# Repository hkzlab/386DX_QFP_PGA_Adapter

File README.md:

# 386DX QFP -> PGA Adapter

## Introduction

386DX CPUs in ceramic PGA packages are getting rarer and more expensive by the day, while QFP variants can still be found relatively easily. But some motherboards don't have a space for a QFP CPU, and they're an hassle to swap anyway.

This project provides a way to adapt the QFP variants of the 386DX cpus to a PGA format, by using commonly available hardware parts.
I tested the procedure on an AM386DX @ 40Mhz, and the machine happily ran memory tests and benchmarks for hours.

### Disclaimer

I take NO responsibility for what happens if you decide to build and use this adapter. But You're encourauged to take what you deem fit from this, and use it in your projects!

## Required components

* The PCB adapter itself, 1.6mm thickness is fine
* The pin holder, 1.6mm thickness
* Stencil for the bottom (PGA) side of the adapter
* Solder paste for SMD work
* Pin sockets, lots of (>132, as some will be bent, out of spec, etc.). 7.54mm for height is a good measure. You can find them on Aliexpress, e.g. [here](https://www.aliexpress.com/item/1005003484780787.html).

### How to build

1. Place the pin holder somewhere raised that leaves you access to the pin holes. I use a "helping hand" soldering tool that pinches the holder at the corners and leaves free the top and bottom of it.
2. Install all the pins from the top. They don't have to snap. It is sufficient that they slide into every hole and stay flush on top. Make sure the height is the same for every pin.
3. Put the QFP-PGA adapter PCB on a flat surface, PGA side (the one with all the "squares") on top.
4. Using the stencil, apply the solder paste evenly on every square where the pins are going to go
5. Carefully lift the adapter PCB, flip it, and put the PGA side on top of the holder with pins (the one currently mounted on the helping hand), making sure that the edges of both PCBs are aligned. You'll get a sandwich of the adapter and holder with the "heads" of the pin in between.
6. Release the holder from the helping hand and flip both the holder and the adapter PCB together, and place them on a flat, heat resistant surface (I use vetronite), with pins pointing towards the ceiling.
7. Turn on your hot air soldering station, and slowly begin soldering all the pins, first heating everything then working on all the sides of the adapter, trying to blow directly on the pins.
8. Pins will start to move slightly, as the flux evaporates. Keep circling around. When they stop moving, they'll have sucked up most of the solder.
9. Wait for everything to cool down, then carefully remove the holder.
10. Inspect with a good light and magnifying glass for shorts between pins. Usually the pins will suck up the excess solder, and you'll probably find no shorts at all. Cut the shorts you find, being careful not to damage the adapter. Also, check that every pin is attached correctly.
11. If you see that some pin has not attached correctly, or is a bit raised than the rest, apply flux, holder, and re-heat.
12. Install the bypass caps if you want them.
13. Reinstall the holder for structural stability. It doesn't have to snap in. It'll hold on pretty well anyway.
14. You can now solder the processor on the completed adapter. Use a soldering iron for this.

Here are some pics at various points of the procedure. Some images refer to a V53 adapter, but the procedure is identical to the one for this CPU.

## Notes

The last tested revision of the board is Rev.1, changes to Rev.3 are minimal and mostly aesthetic, but be warned.

I tested this adapter with an AM386DX @ 40Mhz.

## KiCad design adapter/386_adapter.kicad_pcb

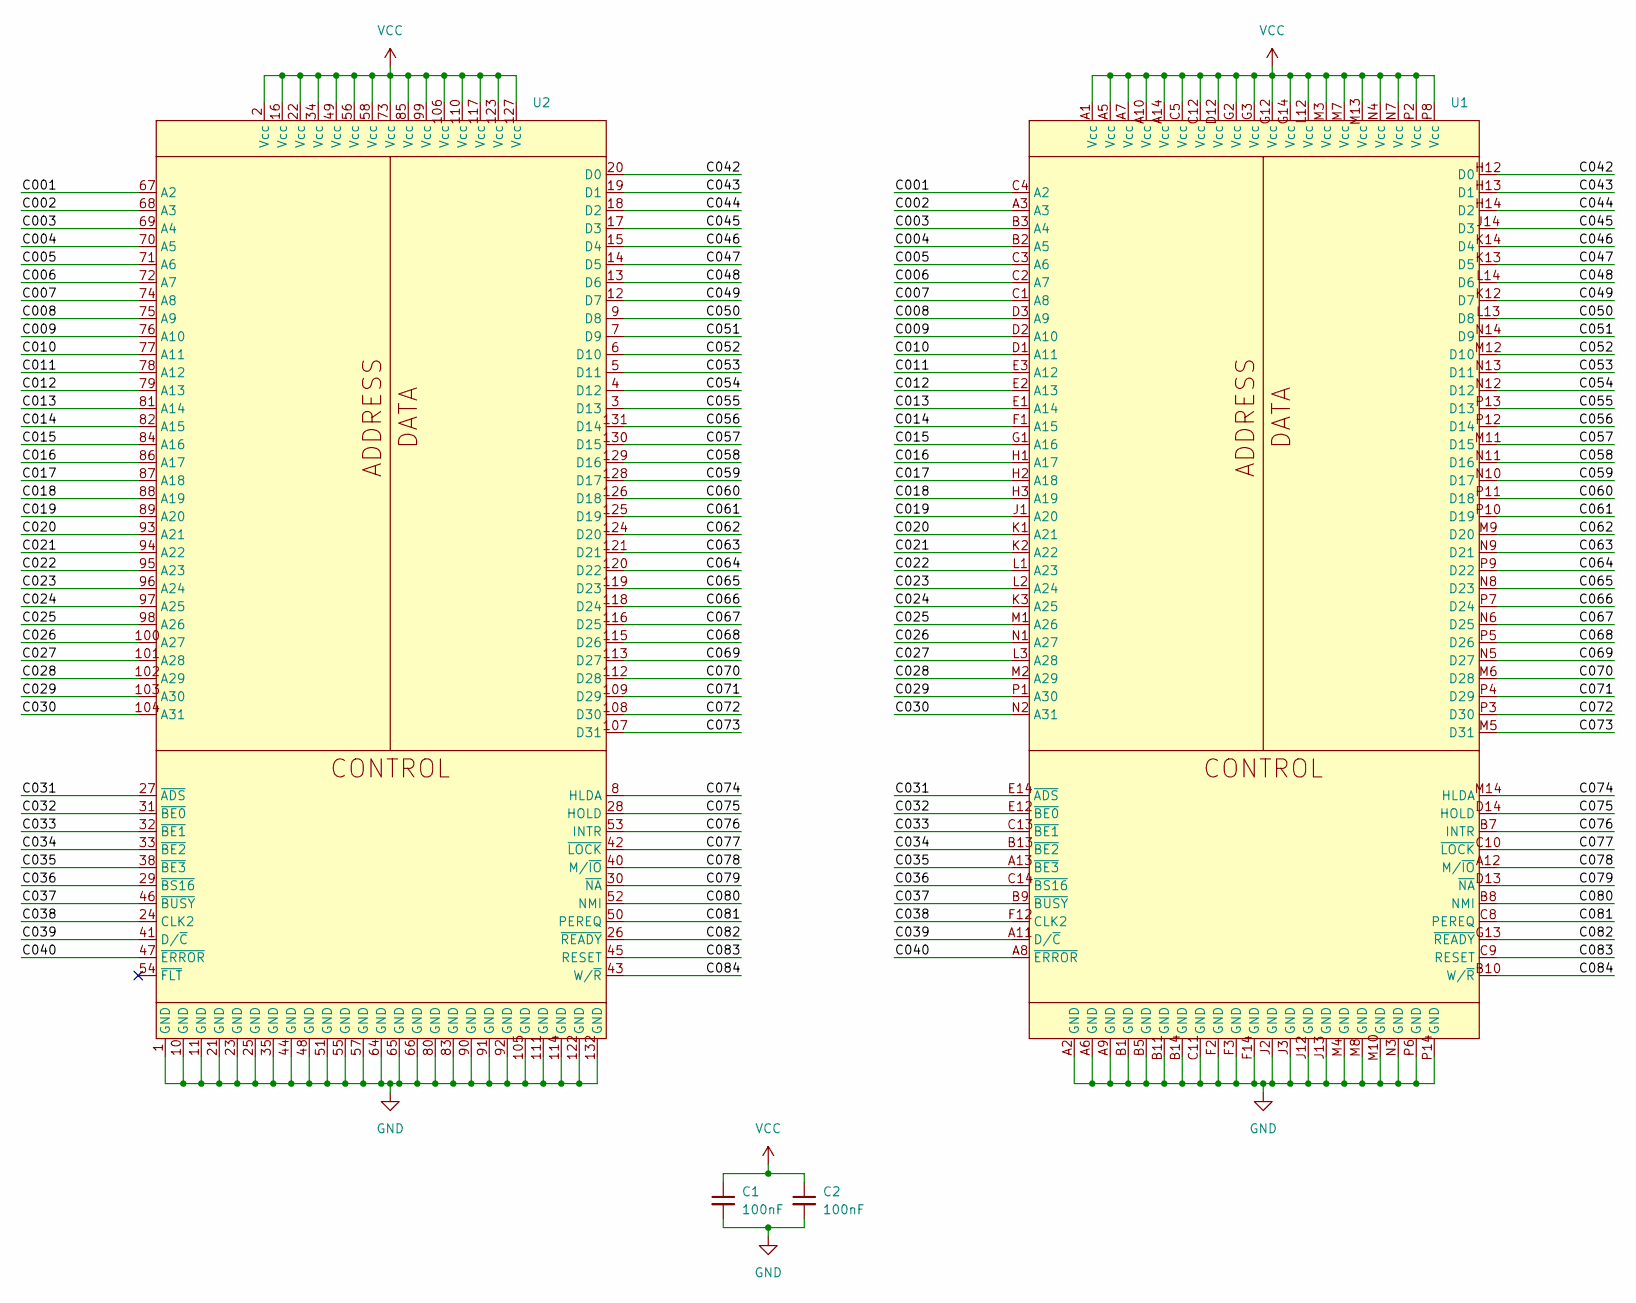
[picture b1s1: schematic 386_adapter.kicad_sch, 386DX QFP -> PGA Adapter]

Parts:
C1, C2: 100nF; C_1206_3216Metric_Pad1.33x1.80mm_HandSolder
U1: PGA-132_SMD
U2: PQFP-132_24x24mm_P0.635mm_i386

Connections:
/C001: U1.C4 (A2), U2.67 (A2)
/C002: U1.A3, U2.68 (A3)
/C003: U1.B3 (A4), U2.69 (A4)
/C004: U1.B2 (A5), U2.70 (A5)
/C005: U1.C3 (A6), U2.71 (A6)
/C006: U1.C2 (A7), U2.72 (A7)
/C007: U1.C1 (A8), U2.74 (A8)
/C008: U1.D3 (A9), U2.75 (A9)
/C009: U1.D2 (A10), U2.76 (A10)
/C010: U1.D1 (A11), U2.77 (A11)
/C011: U1.E3 (A12), U2.78 (A12)
/C012: U1.E2 (A13), U2.79 (A13)
/C013: U1.E1 (A14), U2.81 (A14)
/C014: U1.F1 (A15), U2.82 (A15)
/C015: U1.G1 (A16), U2.84 (A16)
/C016: U1.H1 (A17), U2.86 (A17)
/C017: U1.H2 (A18), U2.87 (A18)
/C018: U1.H3 (A19), U2.88 (A19)
/C019: U1.J1 (A20), U2.89 (A20)
/C020: U1.K1 (A21), U2.93 (A21)
/C021: U1.K2 (A22), U2.94 (A22)
/C022: U1.L1 (A23), U2.95 (A23)
/C023: U1.L2 (A24), U2.96 (A24)
/C024: U1.K3 (A25), U2.97 (A25)
/C025: U1.M1 (A26), U2.98 (A26)
/C026: U1.N1 (A27), U2.100 (A27)
/C027: U1.L3 (A28), U2.101 (A28)
/C028: U1.M2 (A29), U2.102 (A29)
/C029: U1.P1 (A30), U2.103 (A30)
/C030: U1.N2 (A31), U2.104 (A31)
/C031: U1.E14 (~ADS), U2.27 (~ADS)
/C032: U1.E12 (~BE0), U2.31 (~BE0)
/C033: U1.C13 (~BE1), U2.32 (~BE1)
/C034: U1.B13 (~BE2), U2.33 (~BE2)
/C035: U1.A13 (~BE3), U2.38 (~BE3)
/C036: U1.C14 (~BS16), U2.29 (~BS16)
/C037: U1.B9 (~BUSY), U2.46 (~BUSY)
/C038: U1.F12 (CLK2), U2.24 (CLK2)
/C039: U1.A11 (D/~C), U2.41 (D/~C)
/C040: U1.A8 (~ERROR), U2.47 (~ERROR)
/C042: U1.H12 (D0), U2.20 (D0)
/C043: U1.H13 (D1), U2.19 (D1)
/C044: U1.H14 (D2), U2.18 (D2)
/C045: U1.J14 (D3), U2.17 (D3)
/C046: U1.K14 (D4), U2.15 (D4)
/C047: U1.K13 (D5), U2.14 (D5)
/C048: U1.L14 (D6), U2.13 (D6)
/C049: U1.K12 (D7), U2.12 (D7)
/C050: U1.L13 (D8), U2.9 (D8)
/C051: U1.N14 (D9), U2.7 (D9)
/C052: U1.M12 (D10), U2.6 (D10)
/C053: U1.N13 (D11), U2.5 (D11)
/C054: U1.N12 (D12), U2.4 (D12)
/C055: U1.P13 (D13), U2.3 (D13)
/C056: U1.P12 (D14), U2.131 (D14)
/C057: U1.M11 (D15), U2.130 (D15)
/C058: U1.N11 (D16), U2.129 (D16)
/C059: U1.N10 (D17), U2.128 (D17)
/C060: U1.P11 (D18), U2.126 (D18)
/C061: U1.P10 (D19), U2.125 (D19)
/C062: U1.M9 (D20), U2.124 (D20)
/C063: U1.N9 (D21), U2.121 (D21)
/C064: U1.P9 (D22), U2.120 (D22)
/C065: U1.N8 (D23), U2.119 (D23)
/C066: U1.P7 (D24), U2.118 (D24)
/C067: U1.N6 (D25), U2.116 (D25)
/C068: U1.P5 (D26), U2.115 (D26)
/C069: U1.N5 (D27), U2.113 (D27)
/C070: U1.M6 (D28), U2.112 (D28)
/C071: U1.P4 (D29), U2.109 (D29)
/C072: U1.P3 (D30), U2.108 (D30)
/C073: U1.M5 (D31), U2.107 (D31)
/C074: U1.M14 (HLDA), U2.8 (HLDA)
/C075: U1.D14 (HOLD), U2.28 (HOLD)
/C076: U1.B7 (INTR), U2.53 (INTR)
/C077: U1.C10 (~LOCK), U2.42 (~LOCK)
/C078: U1.A12 (M/~IO), U2.40 (M/~IO)
/C079: U1.D13 (~NA), U2.30 (~NA)
/C080: U1.B8 (NMI), U2.52 (NMI)
/C081: U1.C8 (PEREQ), U2.50 (PEREQ)
/C082: U1.G13 (~READY), U2.26 (~READY)
/C083: U1.C9 (RESET), U2.45 (RESET)
/C084: U1.B10 (W/~R), U2.43 (W/~R)
GND: C1.2, C2.2, U1.A2 (GND), U1.A6 (GND), U1.A9 (GND), U1.B1 (GND), U1.B5 (GND), U1.B11 (GND), U1.B14 (GND), U1.C11 (GND), U1.F2 (GND), U1.F3 (GND), U1.F14 (GND), U1.J2 (GND), U1.J3 (GND), U1.J12 (GND), U1.J13 (GND), U1.M4 (GND), U1.M8 (GND), U1.M10 (GND), U1.N3 (GND), U1.P6 (GND), U1.P14 (GND), U2.1 (GND), U2.10 (GND), U2.11 (GND), U2.21 (GND), U2.23 (GND), U2.25 (GND), U2.35 (GND), U2.44 (GND), U2.48 (GND), U2.51 (GND), U2.55 (GND), U2.57 (GND), U2.64 (GND), U2.65 (GND), U2.66 (GND), U2.80 (GND), U2.83 (GND), U2.90 (GND), U2.91 (GND), U2.92 (GND), U2.105 (GND), U2.111 (GND), U2.114 (GND), U2.122 (GND), U2.132 (GND)
VCC: C1.1, C2.1, U1.A1 (Vcc), U1.A5 (Vcc), U1.A7 (Vcc), U1.A10 (Vcc), U1.A14 (Vcc), U1.C5 (Vcc), U1.C12 (Vcc), U1.D12 (Vcc), U1.G2 (Vcc), U1.G3 (Vcc), U1.G12 (Vcc), U1.G14 (Vcc), U1.L12 (Vcc), U1.M3 (Vcc), U1.M7 (Vcc), U1.M13 (Vcc), U1.N4 (Vcc), U1.N7 (Vcc), U1.P2 (Vcc), U1.P8 (Vcc), U2.2 (Vcc), U2.16 (Vcc), U2.22 (Vcc), U2.34 (Vcc), U2.49 (Vcc), U2.56 (Vcc), U2.58 (Vcc), U2.73 (Vcc), U2.85 (Vcc), U2.99 (Vcc), U2.106 (Vcc), U2.110 (Vcc), U2.117 (Vcc), U2.123 (Vcc), U2.127 (Vcc)

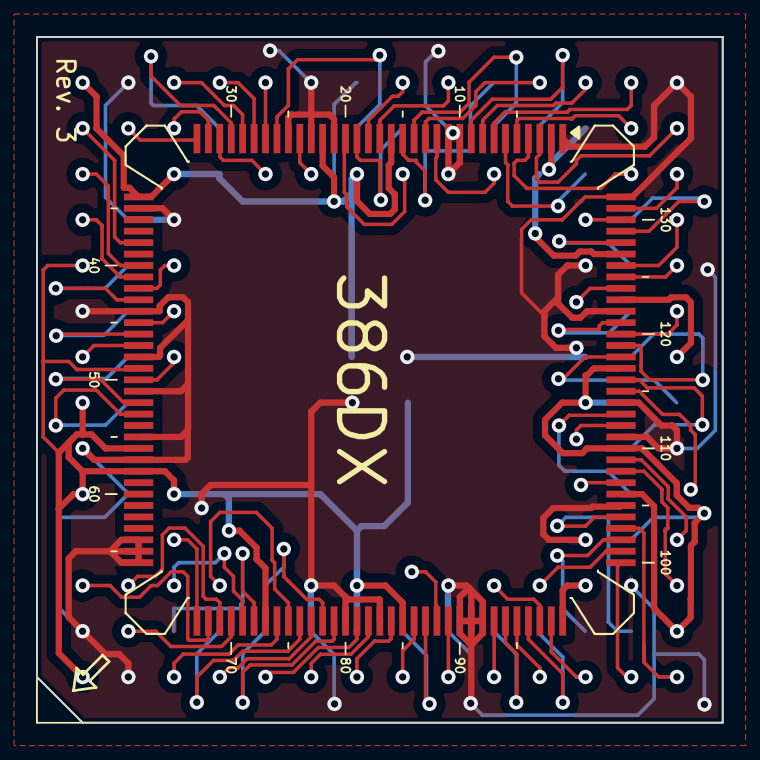
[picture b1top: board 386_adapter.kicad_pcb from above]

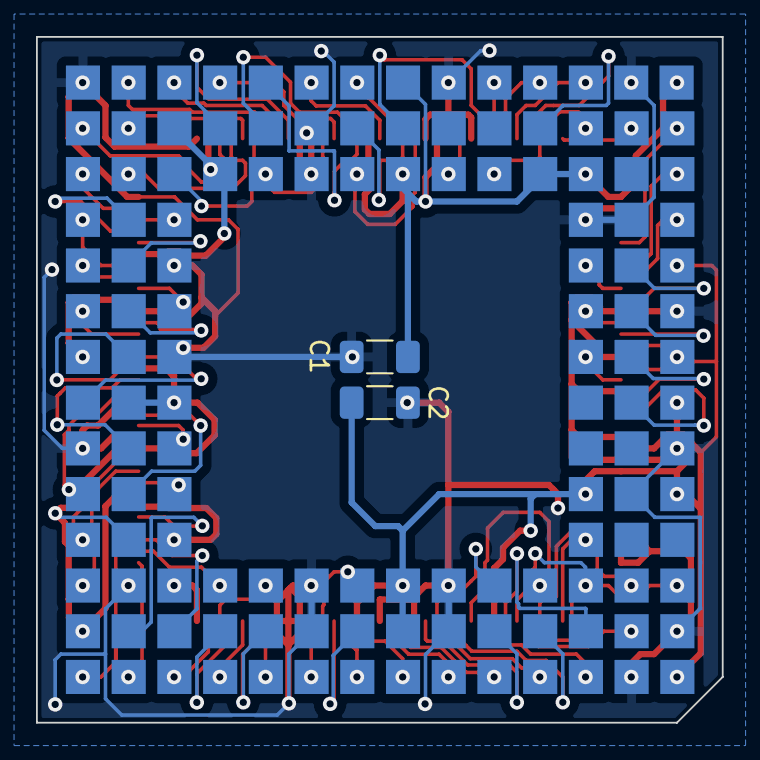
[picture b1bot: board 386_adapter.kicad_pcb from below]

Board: 2 copper layers, 38.1 x 38.1 mm, 4 parts (2 on the bottom side), 85 nets.

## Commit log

2024-02-24 Begin drawing 386 PQFP packag
2024-02-24 Additional symbol drawing
2024-02-24 PQFP symbol
2024-02-24 Begin preparing the PGA footprint
2024-02-24 Advancing PGA footprint
2024-02-24 Draw 386 qfp/pga adapter
2024-02-27 Add gerbers
2024-02-27 Add filter caps
2024-02-27 Added silkscreen
2024-02-27 Update PCB
2024-03-28 Updated project, plus link a GND pad that was previously left without trace
2024-04-02 Update the project and silkscreen
2024-04-14 Some more changes for rev.3
2024-04-26 Update holder schematic and gerber
2024-04-26 Added readme
2024-04-26 Resize pictures
2024-04-26 Further resize
2024-04-26 Tweak the readme
2025-06-02 Add license info
2025-06-02 Fix markdown
2025-06-02 Move license to separate file
2025-06-02 Overwrite license with full text
